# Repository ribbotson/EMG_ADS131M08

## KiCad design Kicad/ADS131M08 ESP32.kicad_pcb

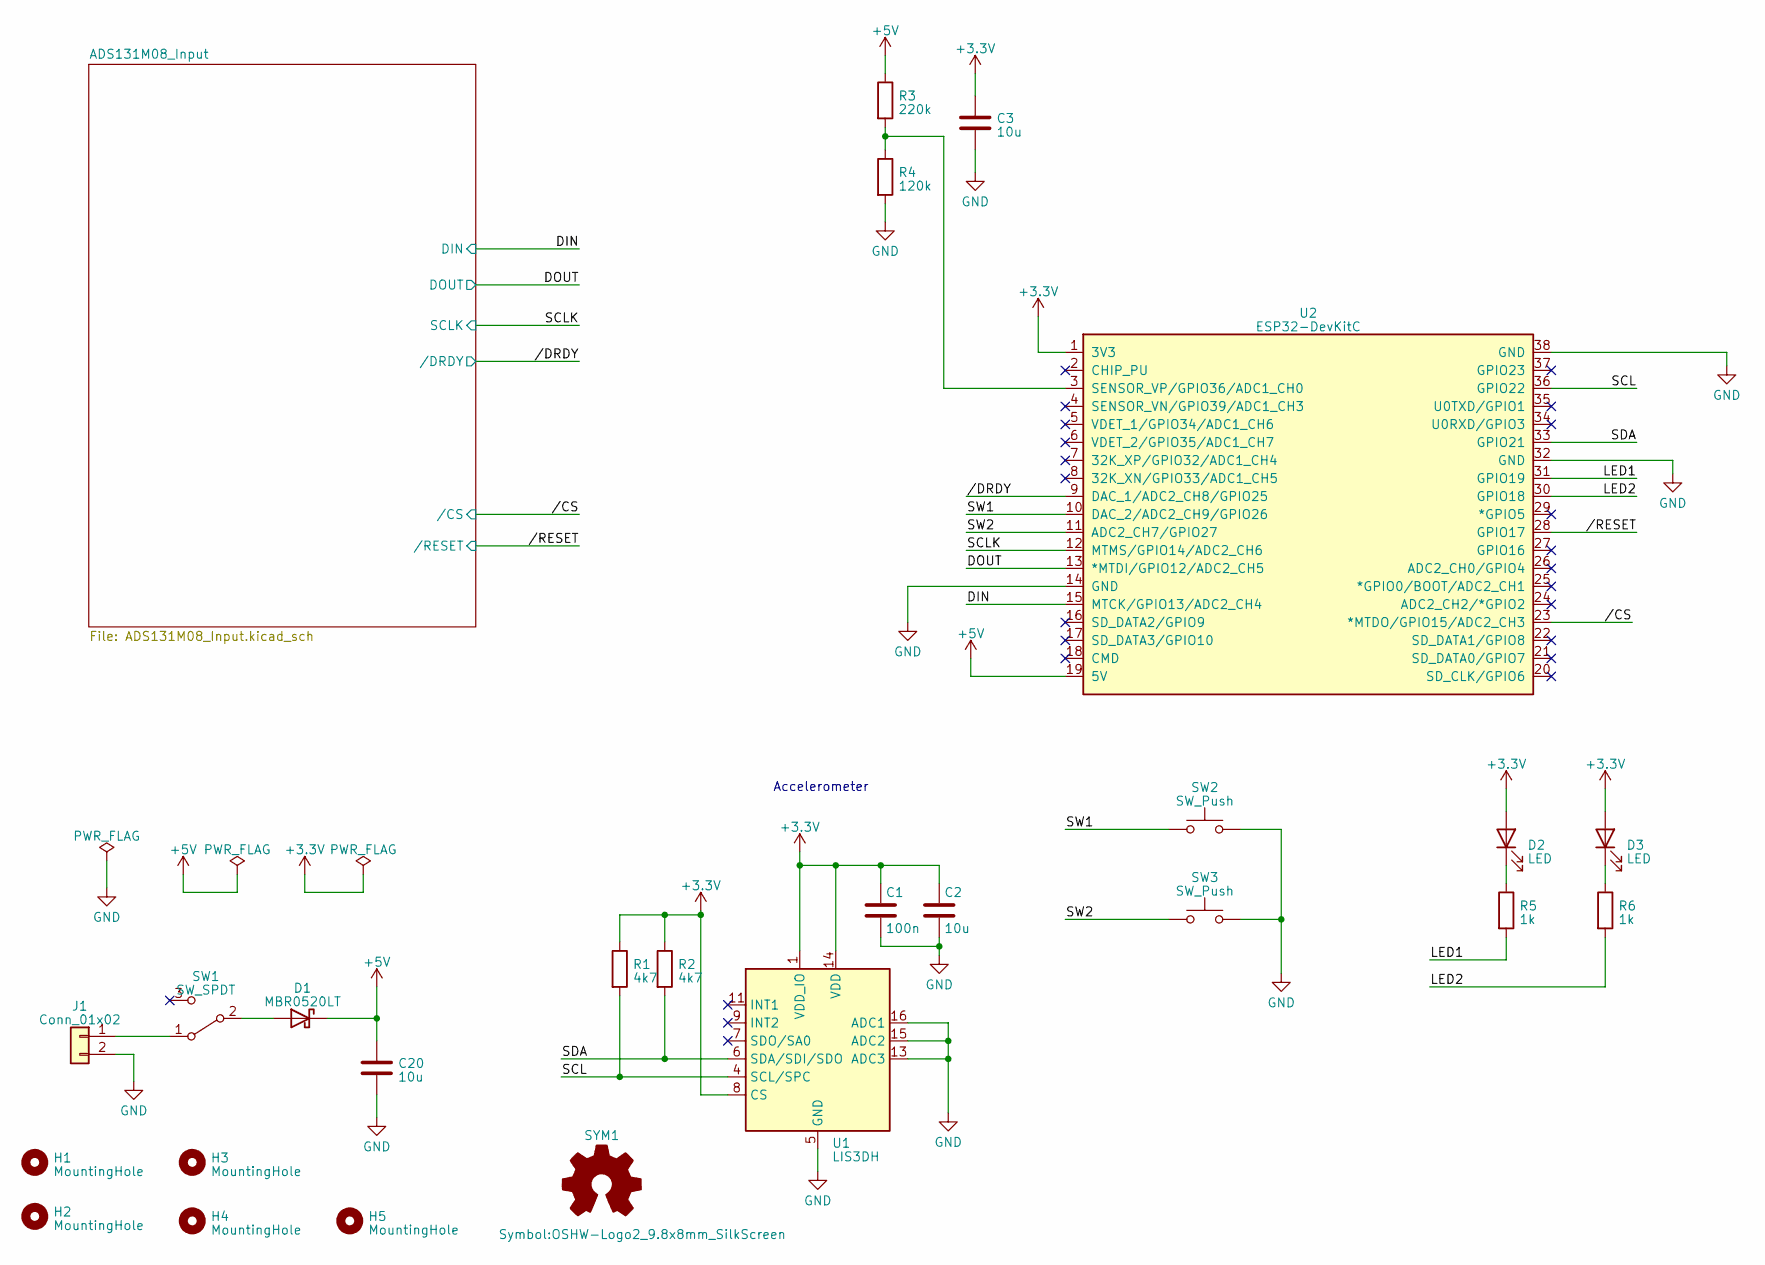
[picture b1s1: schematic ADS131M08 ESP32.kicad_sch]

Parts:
C1: 100n; C_0603_1608Metric
C2, C3, C20: 10u; C_0805_2012Metric
D1: MBR0520LT; D_SOD-123
D2, D3: LED; LED_0603_1608Metric
H1, H2, H3, H4, H5: MountingHole; MountingHole_2.2mm_M2
J1: Conn_01x02; JST_PH_S2B-PH-SM4-TB_1x02-1MP_P2.00mm_Horizontal
R1, R2: 4k7; R_0603_1608Metric
R3: 220k; R_0603_1608Metric
R4: 120k; R_0603_1608Metric
R5, R6: 1k; R_0603_1608Metric
SW1: SW_SPDT; SW_SPDT_CK-JS102011SAQN
SW2, SW3: SW_Push; SW_SPST_EVQP0
SYM1: Logo_Open_Hardware_Small; OSHW-Logo2_9.8x8mm_SilkScreen
U1: LIS3DH; LGA-16_3x3mm_P0.5mm_LayoutBorder3x5y
U2: ESP32-DevKitC

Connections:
+3.3V: C1.1, C2.1, C3.1, D2.2 (A), D3.2 (A), R1.1, R2.1, U1.1 (VDD_IO), U1.8 (CS), U1.14 (VDD), U2.1 (3V3); also elsewhere on the board
+5V: C20.1, D1.1 (K), R3.1, U2.19 (5V); also elsewhere on the board
/DIN: U2.15 (MTCK/GPIO13/ADC2_CH4); also elsewhere on the board
/DOUT: U2.13 (*MTDI/GPIO12/ADC2_CH5); also elsewhere on the board
/LED1: R5.2, U2.31 (GPIO19)
/LED2: R6.2, U2.30 (GPIO18)
/SCL: R1.2, U1.4 (SCL/SPC), U2.36 (GPIO22)
/SCLK: U2.12 (MTMS/GPIO14/ADC2_CH6); also elsewhere on the board
/SDA: R2.2, U1.6 (SDA/SDI/SDO), U2.33 (GPIO21)
/SW1: SW2.1, U2.10 (DAC_2/ADC2_CH9/GPIO26)
/SW2: SW3.1, U2.11 (ADC2_CH7/GPIO27)
//CS: U2.23 (*MTDO/GPIO15/ADC2_CH3); also elsewhere on the board
//DRDY: U2.9 (DAC_1/ADC2_CH8/GPIO25); also elsewhere on the board
//RESET: U2.28 (GPIO17); also elsewhere on the board
GND: C1.2, C2.2, C3.2, C20.2, J1.2, R4.2, SW2.2, SW3.2, U1.5 (GND), U1.10 (GND), U1.12 (GND), U1.13 (ADC3), U1.15 (ADC2), U1.16 (ADC1), U2.14 (GND), U2.32 (GND), U2.38 (GND); also elsewhere on the board
unnamed: D1.2 (A), SW1.2 (B)
unnamed: D2.1 (K), R5.1
unnamed: D3.1 (K), R6.1
unnamed: J1.1, SW1.1 (A)
unnamed: R3.2, R4.1, U2.3 (SENSOR_VP/GPIO36/ADC1_CH0)

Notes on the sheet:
Accelerometer

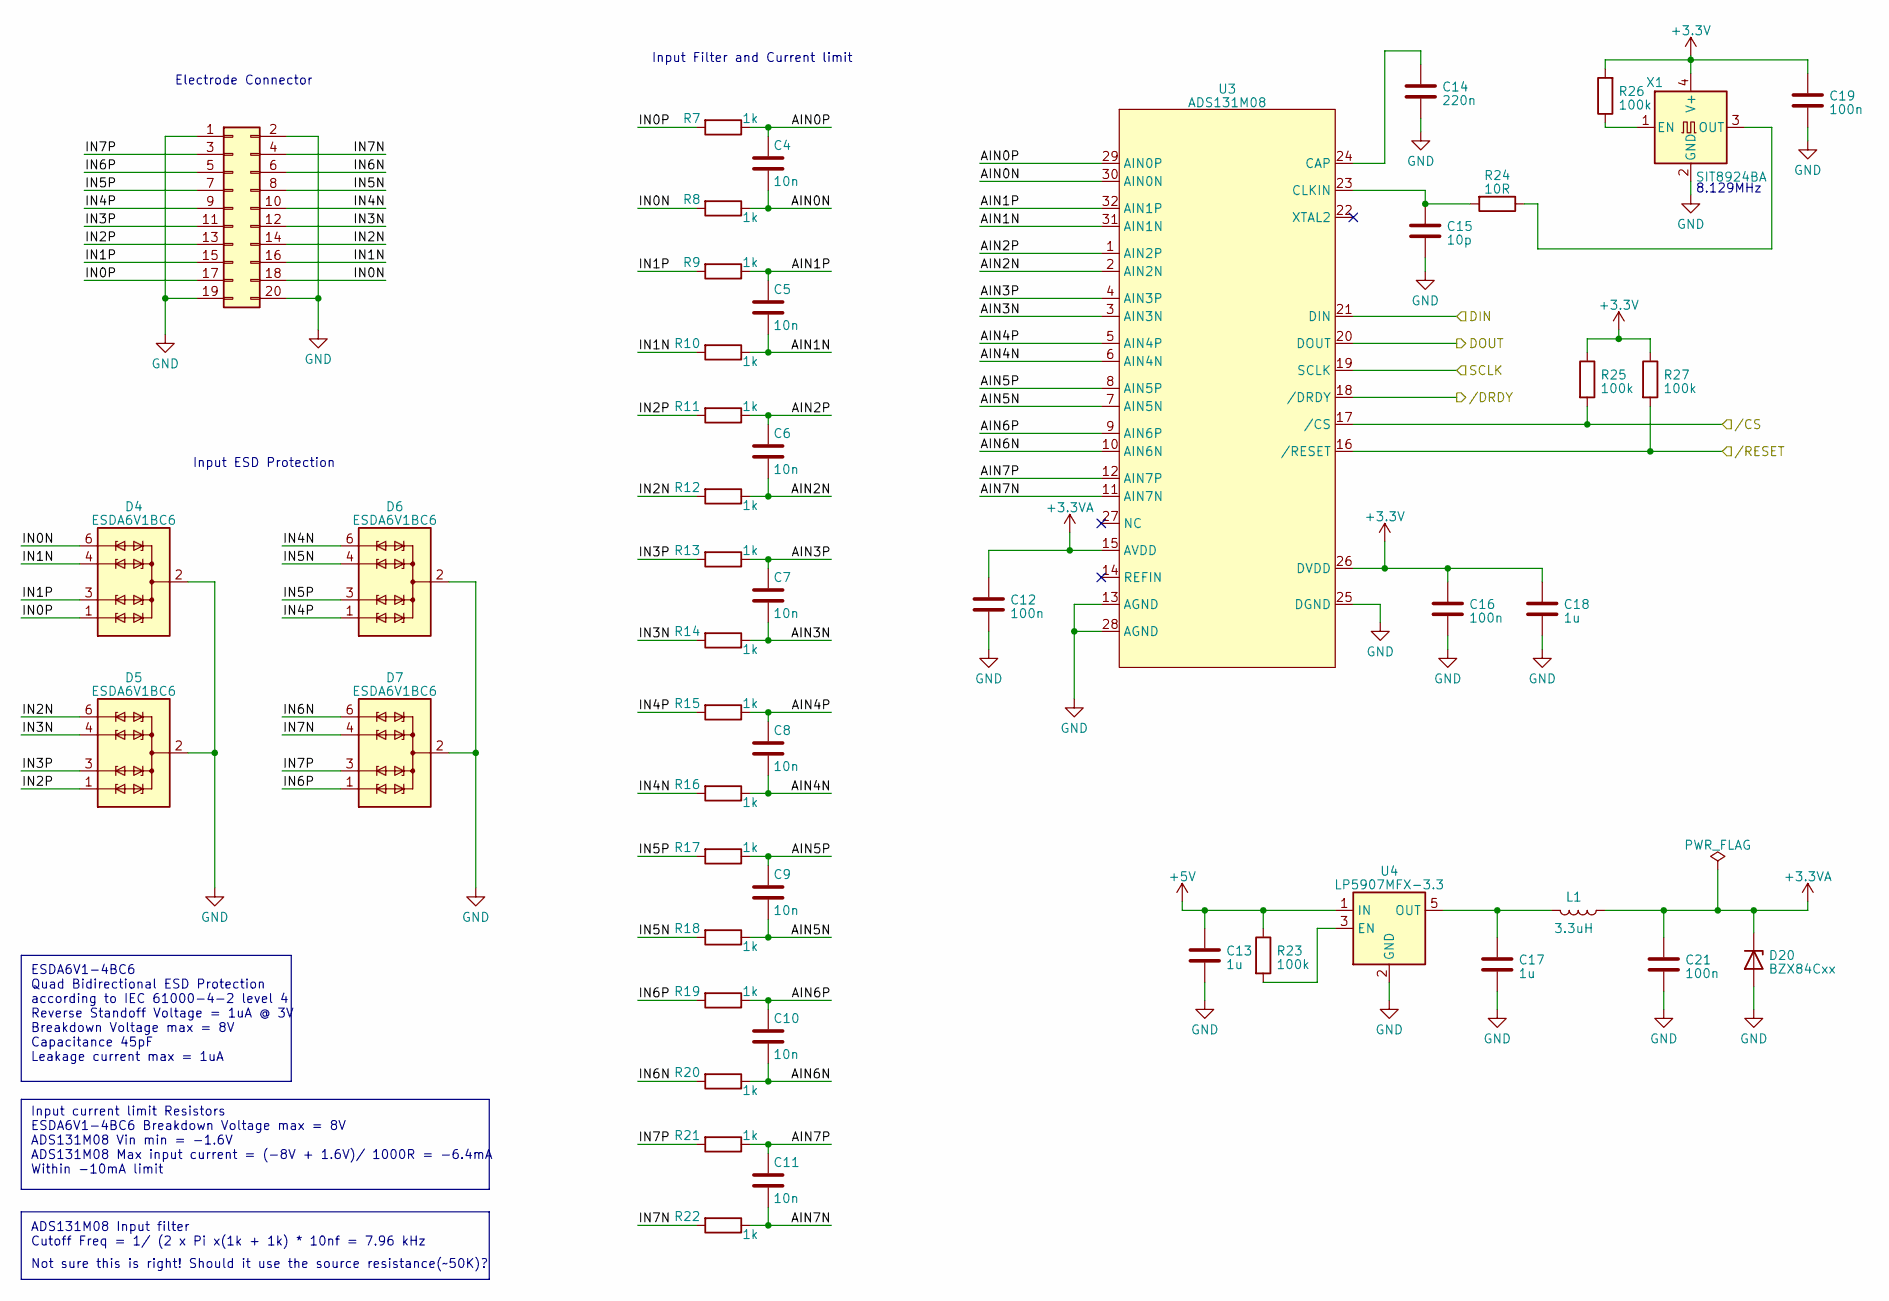
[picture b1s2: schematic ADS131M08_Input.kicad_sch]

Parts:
C4, C5, C6, C7, C8, C9, C10, C11: 10n; C_0603_1608Metric
C12, C16, C19, C21: 100n; C_0603_1608Metric
C13, C17, C18: 1u; C_0603_1608Metric
C14: 220n; C_0603_1608Metric
C15: 10p; C_0603_1608Metric
D4, D5, D6, D7: ESDA6V1BC6; SOT-23-6
D20: BZX84Cxx; SOT-23
J2: Conn_02x10_Odd_Even; PinHeader_2x10_P2.54mm_Horizontal
L1: 3.3uH; L_0603_1608Metric
R7, R8, R9, R10, R11, R12, R13, R14, R15, R16, R17, R18, R19, R20, R21, R22: 1k; R_0603_1608Metric
R23, R25, R26, R27: 100k; R_0603_1608Metric
R24: 10R; R_0603_1608Metric
U3: ADS131M08; PQFP-32_5x5mm_P0.5mm
U4: LP5907MFX-3.3; SOT-23-5
X1: SIT8924BA; Oscillator_SMD_EuroQuartz_XO32-4Pin_3.2x2.5mm

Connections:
+3.3V: C16.1, C18.1, C19.1, R25.1, R26.2, R27.1, U3.26 (DVDD), X1.4 (V+); also elsewhere on the board
+3.3VA: C12.1, C21.1, D20.3 (K), L1.1, U3.15 (AVDD)
+5V: C13.1, R23.1, U4.1 (IN); also elsewhere on the board
/ADS131M08_Input/AIN0N: C4.2, R8.1, U3.30 (AIN0N)
/ADS131M08_Input/AIN0P: C4.1, R7.1, U3.29 (AIN0P)
/ADS131M08_Input/AIN1N: C5.2, R10.1, U3.31 (AIN1N)
/ADS131M08_Input/AIN1P: C5.1, R9.1, U3.32 (AIN1P)
/ADS131M08_Input/AIN2N: C6.2, R12.1, U3.2 (AIN2N)
/ADS131M08_Input/AIN2P: C6.1, R11.1, U3.1 (AIN2P)
/ADS131M08_Input/AIN3N: C7.2, R14.1, U3.3 (AIN3N)
/ADS131M08_Input/AIN3P: C7.1, R13.1, U3.4 (AIN3P)
/ADS131M08_Input/AIN4N: C8.2, R16.1, U3.6 (AIN4N)
/ADS131M08_Input/AIN4P: C8.1, R15.1, U3.5 (AIN4P)
/ADS131M08_Input/AIN5N: C9.2, R18.1, U3.7 (AIN5N)
/ADS131M08_Input/AIN5P: C9.1, R17.1, U3.8 (AIN5P)
/ADS131M08_Input/AIN6N: C10.2, R20.1, U3.10 (AIN6N)
/ADS131M08_Input/AIN6P: C10.1, R19.1, U3.9 (AIN6P)
/ADS131M08_Input/AIN7N: C11.2, R22.1, U3.11 (AIN7N)
/ADS131M08_Input/AIN7P: C11.1, R21.1, U3.12 (AIN7P)
/ADS131M08_Input/IN0N: D4.6 (TVS4), J2.18, R8.2
/ADS131M08_Input/IN0P: D4.1 (TVS1), J2.17, R7.2
/ADS131M08_Input/IN1N: D4.4 (TVS3), J2.16, R10.2
/ADS131M08_Input/IN1P: D4.3 (TVS2), J2.15, R9.2
/ADS131M08_Input/IN2N: D5.6 (TVS4), J2.14, R12.2
/ADS131M08_Input/IN2P: D5.1 (TVS1), J2.13, R11.2
/ADS131M08_Input/IN3N: D5.4 (TVS3), J2.12, R14.2
/ADS131M08_Input/IN3P: D5.3 (TVS2), J2.11, R13.2
/ADS131M08_Input/IN4N: D6.6 (TVS4), J2.10, R16.2
/ADS131M08_Input/IN4P: D6.1 (TVS1), J2.9, R15.2
/ADS131M08_Input/IN5N: D6.4 (TVS3), J2.8, R18.2
/ADS131M08_Input/IN5P: D6.3 (TVS2), J2.7, R17.2
/ADS131M08_Input/IN6N: D7.6 (TVS4), J2.6, R20.2
/ADS131M08_Input/IN6P: D7.1 (TVS1), J2.5, R19.2
/ADS131M08_Input/IN7N: D7.4 (TVS3), J2.4, R22.2
/ADS131M08_Input/IN7P: D7.3 (TVS2), J2.3, R21.2
/DIN: U3.21 (DIN); also elsewhere on the board
/DOUT: U3.20 (DOUT); also elsewhere on the board
/SCLK: U3.19 (SCLK); also elsewhere on the board
//CS: R25.2, U3.17 (/CS); also elsewhere on the board
//DRDY: U3.18 (/DRDY); also elsewhere on the board
//RESET: R27.2, U3.16 (/RESET); also elsewhere on the board
GND: C12.2, C13.2, C14.2, C15.2, C16.2, C17.2, C18.2, C19.2, C21.2, D4.2 (COM), D4.5 (COM), D5.2 (COM), D5.5 (COM), D6.2 (COM), D6.5 (COM), D7.2 (COM), D7.5 (COM), D20.1 (A), J2.1, J2.2, J2.19, J2.20, U3.13 (AGND), U3.25 (DGND), U3.28 (AGND), U4.2 (GND), X1.2 (GND); also elsewhere on the board
unnamed: C14.1, U3.24 (CAP)
unnamed: C15.1, R24.2, U3.23 (CLKIN)
unnamed: R23.2, U4.3 (EN)
unnamed: C17.1, L1.2, U4.5 (OUT)
unnamed: R26.1, X1.1 (EN)
unnamed: R24.1, X1.3 (OUT)

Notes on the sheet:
ESDA6V1-4BC6 Quad Bidirectional ESD Protection according to IEC 61000-4-2 level 4 Reverse Standoff Voltage = 1uA @ 3V Breakdown Voltage max = 8V Capacitance 45pF Leakage current max = 1uA
Input Filter and Current limit
Input ESD Protection
8.129MHz
Not sure this is right! Should it use the source resistance(~50K)?
ADS131M08 Input filter Cutoff Freq = 1/ (2 x Pi x(1k + 1k) * 10nf = 7.96 kHz
Electrode Connector
Input current limit Resistors ESDA6V1-4BC6 Breakdown Voltage max = 8V ADS131M08 Vin min = -1.6V ADS131M08 Max input current = (-8V + 1.6V)/ 1000R = -6.4mA Within -10mA limit

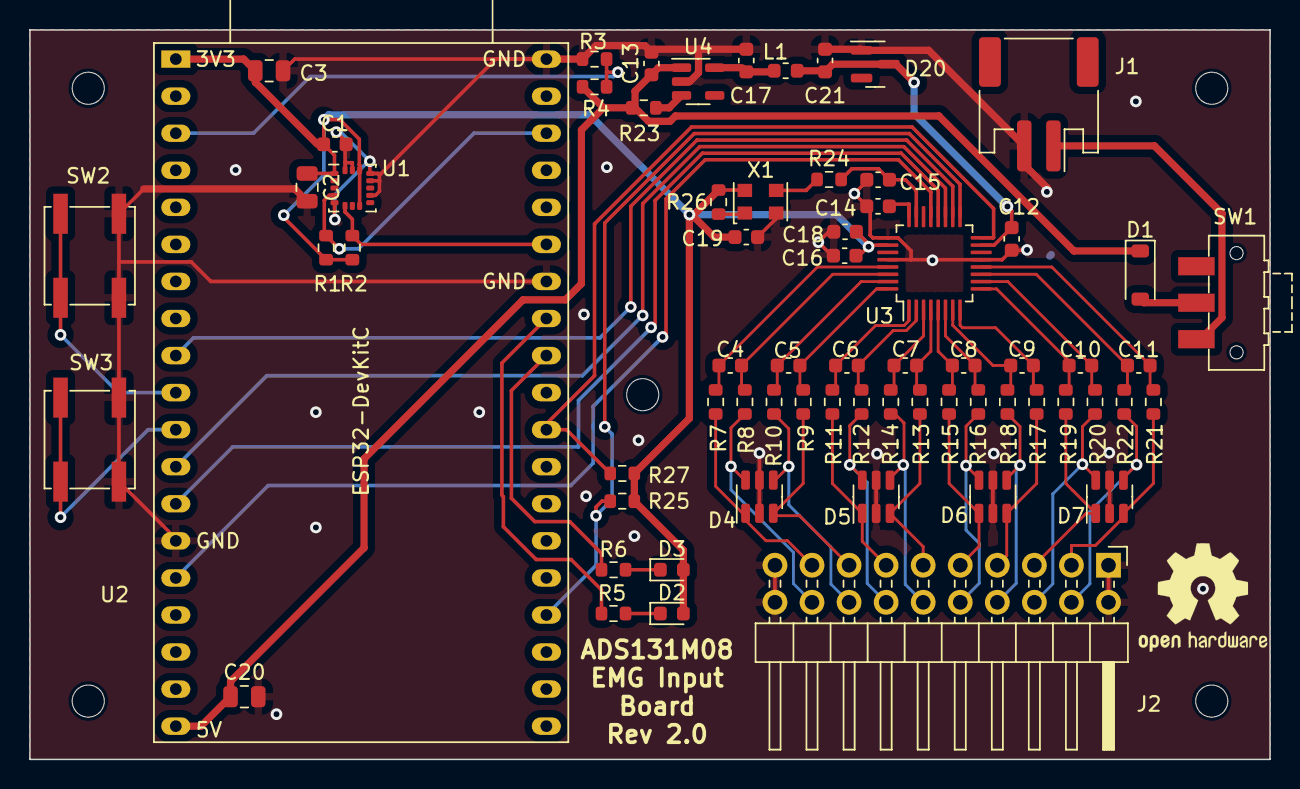
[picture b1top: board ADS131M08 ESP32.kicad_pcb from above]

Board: 2 copper layers, 85.0 x 50.0 mm, 73 parts (0 on the bottom side), 59 nets.

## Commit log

2023-04-21 Fix PCB Issues
    Fix ADS131M08 Pinout
    Fix ADS131M08 footprint size
    Replace tiny ESD devices
2023-04-27 New Gerbers
2023-05-13 add firmware tests
